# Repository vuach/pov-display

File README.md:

# POV Display Rev C

Учебный прототип двухлопастного POV-дисплея с адресными светодиодами APA102.
Питание вращающейся части передаётся бесконтактно индуктивной парой. Скользящие
контакты в Rev C не применяются.

## Итоговая конфигурация

- привод: A2212/13T 1000 KV, ESC 30 A, Li-Po 3S 1500 мА·ч;
- неподвижный контроллер: ESP32-C3 SuperMini, PWM ESC — GPIO6;
- питание ротора: коаксиальная индуктивная пара TX/RX;
- роторный контроллер: ESP32-C3 SuperMini, SN74AHCT125 и Hall-датчик;
- индикация: 40 APA102, две последовательные ветви по 20 LED;
- механика: металлическая ступица, симметричная лопасть и защитный кожух.

## Результат работы

Собранная система Rev C прошла функциональную отладку. Подтверждена работа
питания, бесконтактной передачи энергии, управления ESC и двигателем,
Hall-синхронизации, преобразователя уровней и светодиодной ленты. Итоговые
прошивки для стационарной и вращающейся ESP32-C3 собираются в PlatformIO.

## Содержание

- `docs/` — спецификация, архитектура, решения, результаты и анализ рисков;
- `hardware/` — ведомость компонентов, PCB-S2 и электрические соединения;
- `mechanical/` — измерения, механическая компоновка, CAD и STL;
- `firmware/` — итоговые прошивки ESP32-C3;
- `tests/` — протоколы выполненных проверок;
- `references/` — исходные справочные материалы.

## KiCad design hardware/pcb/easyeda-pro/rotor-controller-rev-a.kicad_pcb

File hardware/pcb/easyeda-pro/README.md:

# EasyEDA Pro

`pcb-s2-rev-c.epro2` — редактируемый исходник PCB-S2 Rev C. Gerber-экспорт
расположен в `../gerber/pcb-s2-rev-c/`.

Фактическая конфигурация: R1 снят, PWM ESC реализован перемычкой
GPIO6 → J3.3, ввод питания платы организован через D1.

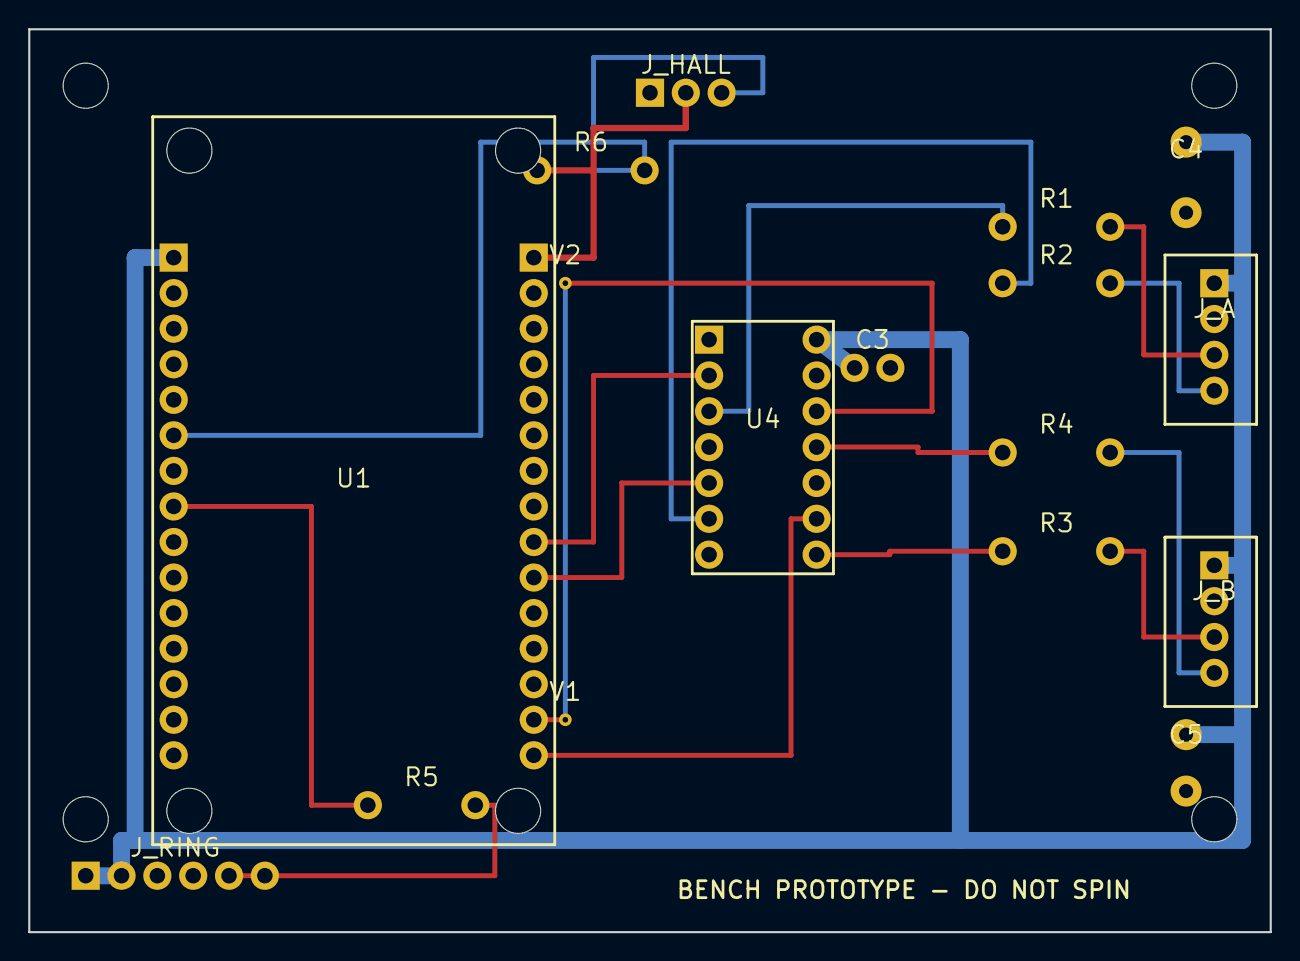
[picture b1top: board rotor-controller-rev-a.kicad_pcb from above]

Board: 2 copper layers, 88.0 x 64.0 mm, 25 parts (0 on the bottom side), 18 nets.

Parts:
C3: C3
C4: C4
C5: C5
J_A: J_A
J_B: J_B
J_HALL: J_HALL
J_RING: J_RING
PCB-M3, PCB-M3#2, PCB-M3#3, PCB-M3#4: NPTH 3.2mm; PCB-M3
R1: R1
R2: R2
R3: R3
R4: R4
R5: R5
R6: R6
U1: U1
U1-MOUNT, U1-MOUNT#2, U1-MOUNT#3, U1-MOUNT#4: NPTH 3.2mm; U1-MOUNT
U4: U4
V1: V1
V2: V2

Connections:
3V3: J_HALL.2, R6.1, U1.R1-3V3
5V: C3.1, C4.1, C5.1, J_A.1, J_B.1, J_RING.1, J_RING.2, U1.L1-VIN, U4.14
CLOCK_A: J_A.4, R2.2
CLOCK_A_3V3: U1.R10-D19, U4.5
CLOCK_A_BUF: R2.1, U4.6
CLOCK_B: J_B.4, R4.2
CLOCK_B_3V3: U1.R14-D22, U4.12, V1.1, V2.1
CLOCK_B_BUF: R4.1, U4.11
DATA_A: J_A.3, R1.2
DATA_A_3V3: U1.R9-D18, U4.2
DATA_A_BUF: R1.1, U4.3
DATA_B: J_B.3, R3.2
DATA_B_3V3: U1.R15-D23, U4.9
DATA_B_BUF: R3.1, U4.8
ESC_PWM: J_RING.5, R5.2
ESC_PWM_3V3: R5.1, U1.L8-D25
GND: C3.2, C4.2, C5.2, J_A.2, J_B.2, J_HALL.1, J_RING.3, J_RING.4, U1.L2-GND, U1.R2-GND, U4.1, U4.4, U4.7, U4.10, U4.13
HALL: J_HALL.3, R6.2, U1.L6-D27
